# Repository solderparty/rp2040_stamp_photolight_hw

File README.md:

# RP2040 Stamp Photo Light (Flux Project)

This Flux Project transforms the RP2040 Stamp into a minimalistic 4x4 NeoPixel matrix. The board contains a **three-way switch**, a **Qwiic** connector, a **LiPo** connector, USB Type-C socket, and a **power switch**.

As the Photo Light is powered by the Stamp, you can run **CircuitPython** on it, as well as **Arduino**.

# Details

Make sure you use a 3.7V/4.2V LiPo with the Photo Light.

The board contains four M2.5 mounting holes, which could be used to attach a diffuser or a case to hold the battery.

# What does "Flux Project" mean?

At Solder Party, we always want to get interesting products in people's hands. However, releasing a product is no easy feat, we need to make sure everything is polished, provide documentation, examples, and extensive support.

With Flux, we want to streamline the process a bit, get fun projects into everyone's hands quicker.

Flux projects are more experimental in nature. While they are tested and verified, the documentation might not be fully there, and the examples might be very basic. 
Flux projects are targeted at people who are not scared to put a bit of extra work into getting the project to where they want it to end up.
These projects are also produced in smaller quantities, there is no guarantee there will be more produced in the future. Even if there is a new batch, it might differ from the initial version. 

These projects are in constant Flux, so to speak.

If there is enough interest, a Flux project might become a fully-fledged Solder Party product in the future, but there is no guarantee.

# Links

For more information visit https://flux.solder.party/

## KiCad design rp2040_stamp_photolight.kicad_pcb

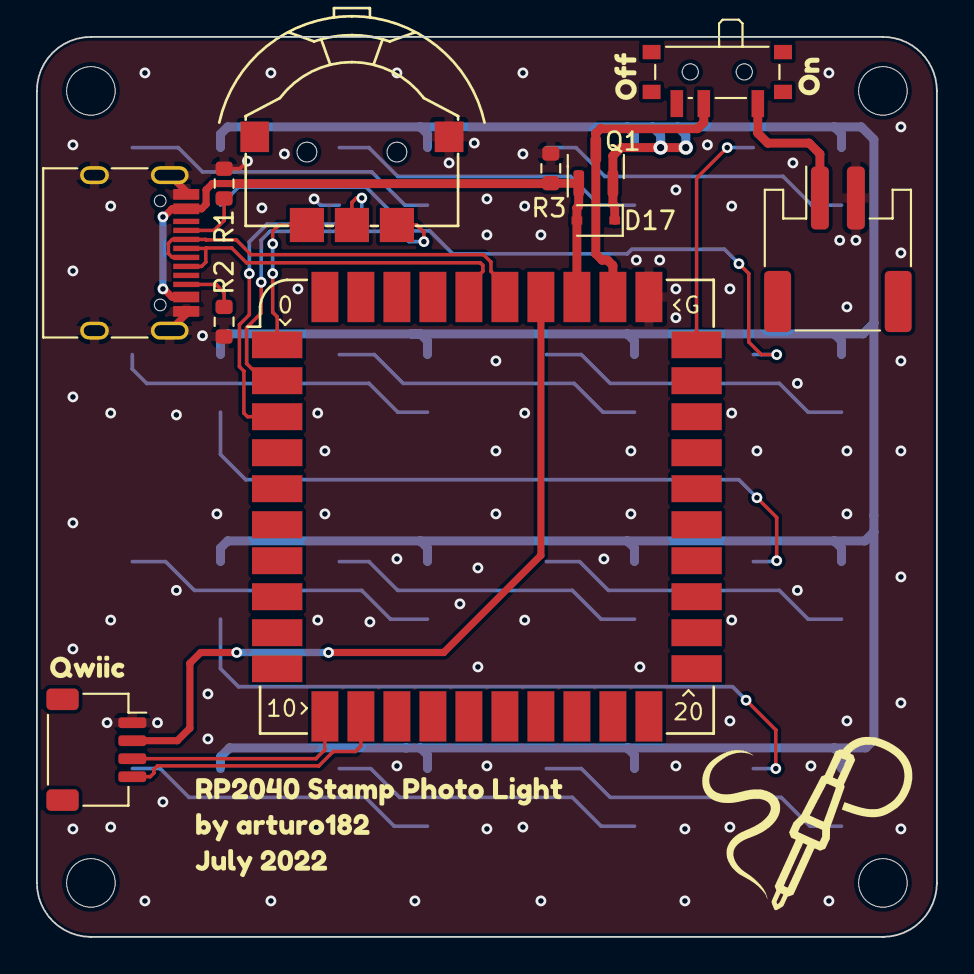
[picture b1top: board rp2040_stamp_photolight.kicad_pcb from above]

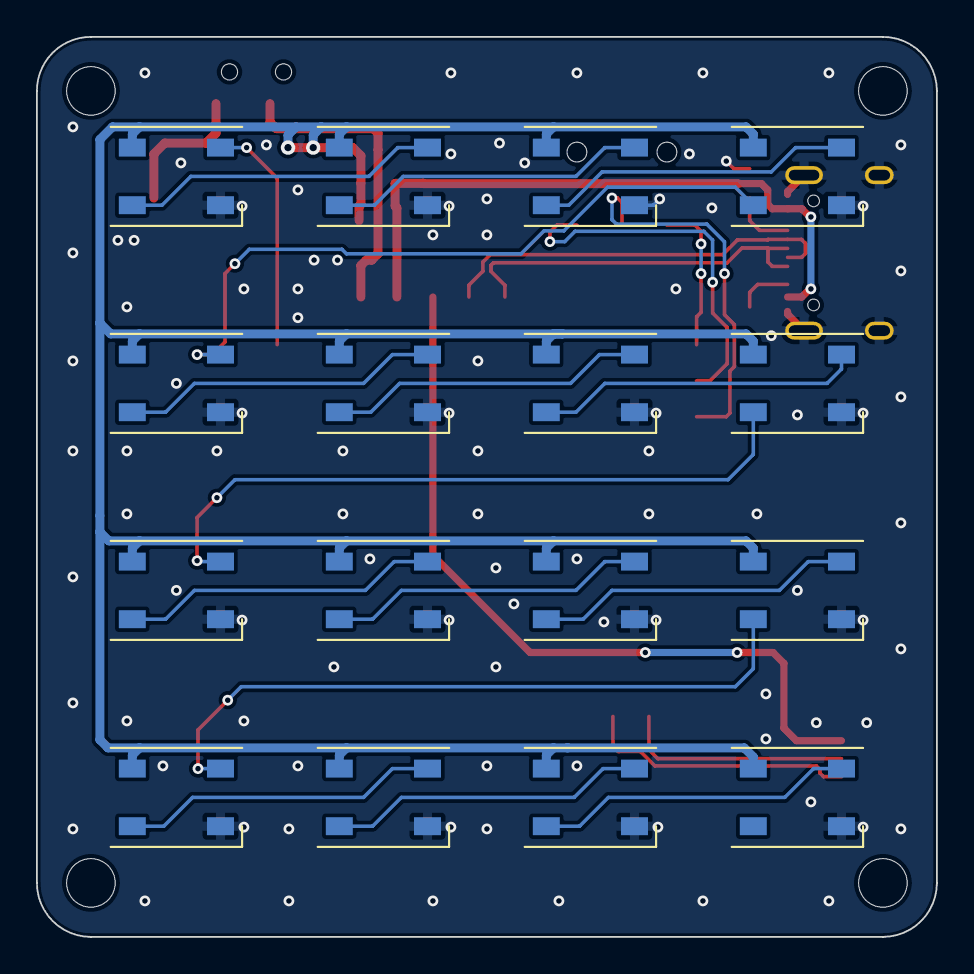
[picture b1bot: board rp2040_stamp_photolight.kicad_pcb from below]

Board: 2 copper layers, 50.0 x 50.0 mm, 31 parts (16 on the bottom side), 31 nets.

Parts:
D1, D2, D3, D4, D5, D6, D7, D8, D9, D10, D11, D12, D13, D14, D15, D16: WS2812C; LED_WS2812B_PLCC4_5.0x5.0mm_P3.2mm
D17: D_Schottky_Small; D_SOD-323
J1: USB_C_Receptacle_USB2.0; USB_C_Receptacle_HRO_TYPE-C-31-M-12
J2: Conn_Qwiic; JST_SH_SM04B-SRSS-TB_1x04-1MP_P1.00mm_Horizontal
J3: Conn_Batt; JST_PH_S2B-PH-SM4-TB_1x02-1MP_P2.00mm_Horizontal
Q1: BSS84; SOT-23
R1, R2: 5.1K; R_0603_1608Metric
R3: 100K; R_0603_1608Metric
SW1: SW_POWER; SW_SPDT_PCM12
U1: RP2040_Stamp; RP2040_Stamp_SMD
U2: SW_Rocker; MCPL3-AC-V
kibuzzard-62CB65A7: G***; kibuzzard-62CB65A7
kibuzzard-62CB65FC: G***; kibuzzard-62CB65FC
kibuzzard-62CB6586: G***; kibuzzard-62CB6586
kibuzzard-62CB6590: G***; kibuzzard-62CB6590

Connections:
+3.3V: J2.2, U1.34 (3.3V)
+5V: D17.2 (A), J1.A4 (VBUS), J1.A9 (VBUS), J1.B4 (VBUS), J1.B9 (VBUS), Q1.1 (G), R3.2, U1.33 (5V)
+BATT: Q1.3 (D), SW1.2 (B), U1.32 (VBAT)
/NEOPIXEL: D1.4 (DIN), U1.30 (GPIO29)
/SCL: J2.4, U1.12 (GPIO11)
/SDA: J2.3, U1.11 (GPIO10)
/SW_CENTER: U1.3 (GPIO2), U2.T
/SW_LEFT: U1.2 (GPIO1), U2.2
/SW_RIGHT: U1.1 (GPIO0), U2.1
/USB_D+: J1.A6 (D+), J1.B6 (D+), U1.36 (USB_D+)
/USB_D-: J1.A7 (D-), J1.B7 (D-), U1.35 (USB_D-)
GND: D1.3 (VSS), D2.3 (VSS), D3.3 (VSS), D4.3 (VSS), D5.3 (VSS), D6.3 (VSS), D7.3 (VSS), D8.3 (VSS), D9.3 (VSS), D10.3 (VSS), D11.3 (VSS), D12.3 (VSS), D13.3 (VSS), D14.3 (VSS), D15.3 (VSS), D16.3 (VSS), J1.A1 (GND), J1.A12 (GND), J1.B1 (GND), J1.B12 (GND), J1.S1 (SHIELD), J2.1, J3.2, R1.2, R2.2, R3.1, U1.31 (GND), U2.C
unnamed: D1.2 (DOUT), D2.4 (DIN)
unnamed: D2.2 (DOUT), D3.4 (DIN)
unnamed: D3.2 (DOUT), D4.4 (DIN)
unnamed: D4.2 (DOUT), D5.4 (DIN)
unnamed: D5.2 (DOUT), D6.4 (DIN)
unnamed: D6.2 (DOUT), D7.4 (DIN)
unnamed: D7.2 (DOUT), D8.4 (DIN)
unnamed: D8.2 (DOUT), D9.4 (DIN)
unnamed: D10.2 (DOUT), D11.4 (DIN)
unnamed: D9.2 (DOUT), D10.4 (DIN)
unnamed: D11.2 (DOUT), D12.4 (DIN)
unnamed: D12.2 (DOUT), D13.4 (DIN)
unnamed: D13.2 (DOUT), D14.4 (DIN)
unnamed: D14.2 (DOUT), D15.4 (DIN)
unnamed: D15.2 (DOUT), D16.4 (DIN)
unnamed: J1.A5 (CC1), R1.1
unnamed: J1.B5 (CC2), R2.1
unnamed: J3.1, SW1.1 (A)
VDD: D1.1 (VDD), D2.1 (VDD), D3.1 (VDD), D4.1 (VDD), D5.1 (VDD), D6.1 (VDD), D7.1 (VDD), D8.1 (VDD), D9.1 (VDD), D10.1 (VDD), D11.1 (VDD), D12.1 (VDD), D13.1 (VDD), D14.1 (VDD), D15.1 (VDD), D16.1 (VDD), D17.1 (K), Q1.2 (S)

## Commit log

2022-09-21 Rev 1
